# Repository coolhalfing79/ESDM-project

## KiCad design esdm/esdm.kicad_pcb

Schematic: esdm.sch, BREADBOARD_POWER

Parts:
C1, C2: 10uF; C_0805_2012Metric_Pad1.15x1.40mm_HandSolder
C3, C4: 22uF; C_0805_2012Metric_Pad1.15x1.40mm_HandSolder
D1: LED_ALT; LED_D3.0mm
J1: Barrel_Jack; BarrelJack_CUI_PJ-102AH_Horizontal
J2, J3: Conn_02x02_Odd_Even; PinHeader_2x02_P2.54mm_Vertical
R1: 1K; R_0805_2012Metric_Pad1.15x1.40mm_HandSolder
U1: AZ1117-3.3; SOT-223-3_TabPin2
U2: AZ1117-5.0; SOT-223-3_TabPin2

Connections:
GND: C1.2, C2.2, C3.2, C4.2, D1.1, J1.2, J2.3, J2.4, J3.3, J3.4, U1.1, U2.1
unnamed: C1.1, C2.1, J1.1, U1.3, U2.3
unnamed: C3.1, J3.1, J3.2, U1.2
unnamed: C4.1, J2.1, J2.2, R1.1, U2.2
unnamed: D1.2, R1.2

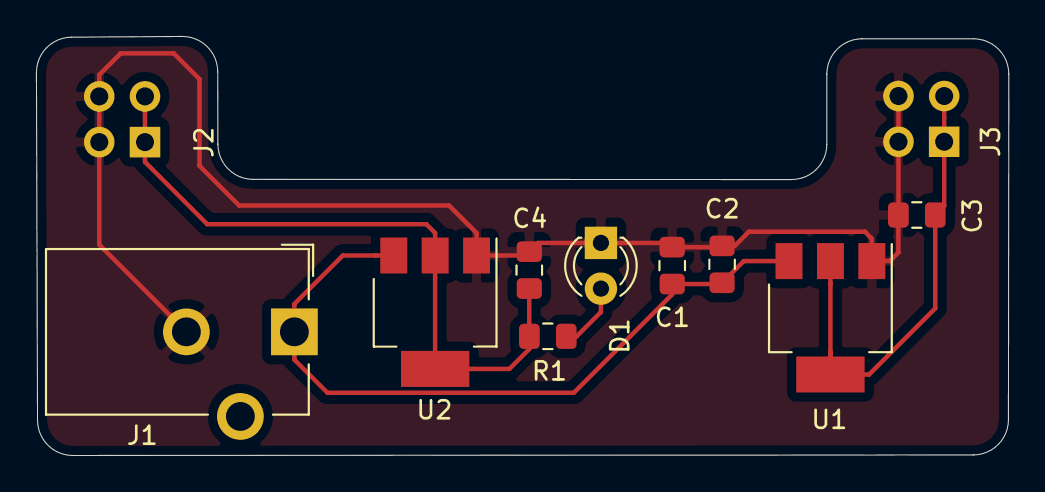
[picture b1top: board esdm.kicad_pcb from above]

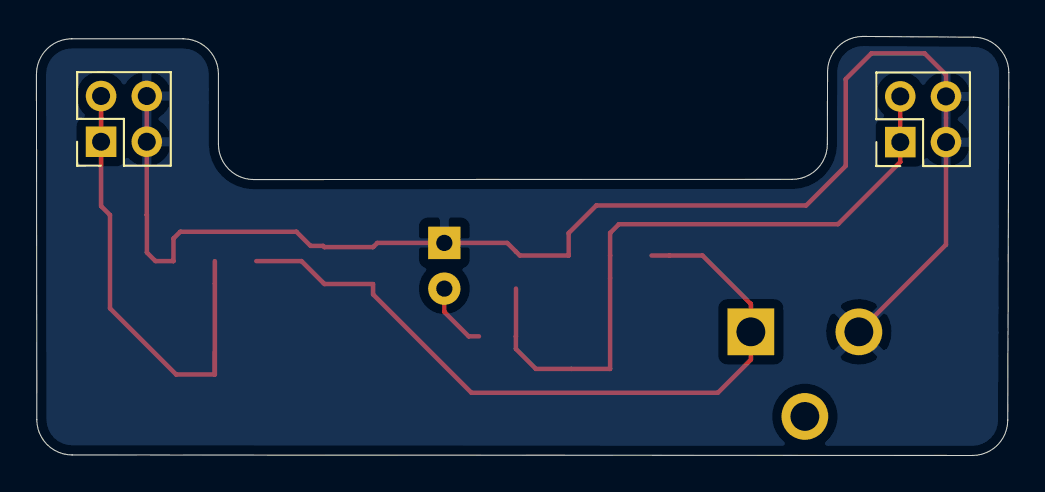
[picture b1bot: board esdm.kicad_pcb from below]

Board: 2 copper layers, 54.0 x 23.3 mm, 11 parts (2 on the bottom side), 5 nets.

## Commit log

2020-02-13 added files
2020-03-08 added experiment 3
2020-03-08 corrected exp 3
2020-03-17 designed the counter circuit
2020-03-17 rearranged directory
2020-03-18 added sub-sheets
2020-03-19 supressed errors
2020-03-19 added correct labels, supressed errors
2020-03-19 added image conversion code
2020-03-23 added eeprom library
2020-03-23 removed interface sheet, combined with pixel_memory
2020-03-26 made interconnects
2020-03-27 added pixel memory to display image
2020-03-27 made interconnections between sheets
2020-04-15 footprints
2020-04-15 please dont break
2020-04-16 added routes
